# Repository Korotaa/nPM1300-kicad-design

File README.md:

# nPM1300-kicad-design

- Power Management IC
- USB type c receptacle
- Very low capacitance ESD protection : SOT23-6L
- 4 layers PCB with 2 signals layer, 1 power plane (GND) and mixed layer

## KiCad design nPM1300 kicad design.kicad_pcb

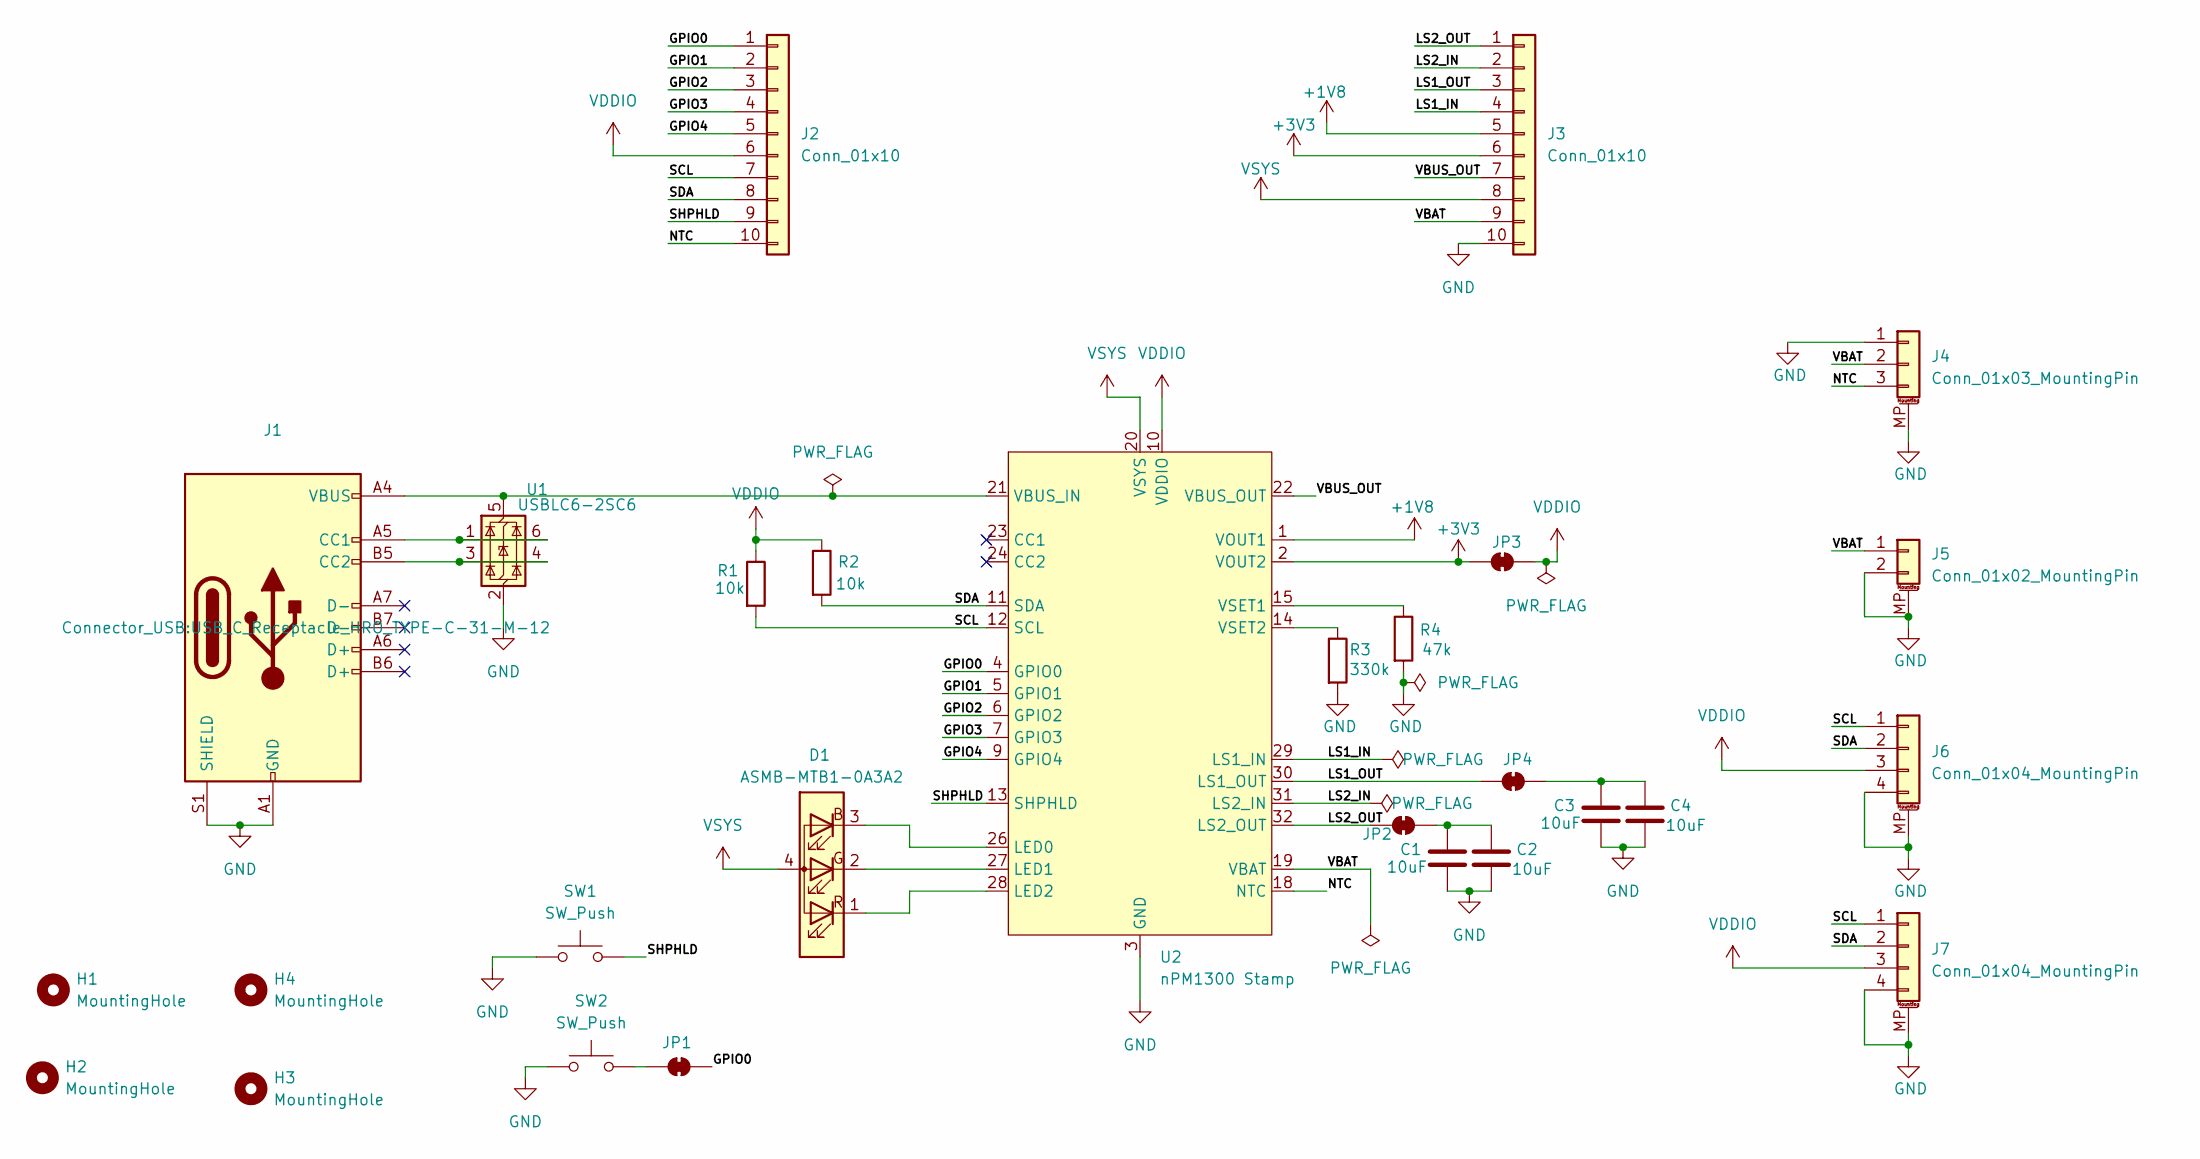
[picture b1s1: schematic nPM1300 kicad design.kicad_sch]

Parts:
C1, C2, C3, C4: 10uF; C_0603_1608Metric_Pad1.08x0.95mm_HandSolder
D1: ASMB-MTB1-0A3A2; LED_Avago_PLCC4_3.2x2.8mm_CW
H1, H2, H3, H4: MountingHole; MountingHole_2.2mm_M2_DIN965_Pad
J1: USB_C_Receptacle_USB2.0_14P; USB_C_Receptacle_HRO_TYPE-C-31-M-12
J2, J3: Conn_01x10; PinHeader_1x10_P1.00mm_Vertical
J4: Conn_01x03_MountingPin; JST_SH_SM03B-SRSS-TB_1x03-1MP_P1.00mm_Horizontal
J5: Conn_01x02_MountingPin; JST_SH_SM02B-SRSS-TB_1x02-1MP_P1.00mm_Horizontal
J6, J7: Conn_01x04_MountingPin; JST_SH_SM04B-SRSS-TB_1x04-1MP_P1.00mm_Horizontal
JP1, JP2, JP3, JP4: SolderJumper_2_Bridged; SolderJumper-2_P1.3mm_Bridged_Pad1.0x1.5mm
R1, R2: 10k; R_0402_1005Metric_Pad0.72x0.64mm_HandSolder
R3: 330k; R_0402_1005Metric_Pad0.72x0.64mm_HandSolder
R4: 47k; R_0402_1005Metric_Pad0.72x0.64mm_HandSolder
SW1, SW2: SW_Push; SW_Push_1P1T_NO_Vertical_Wuerth_434133025816
U1: USBLC6-2SC6; SOT-23-6
U2: nPM1300 Stamp; nPM1300-Stamp_18x18_Pitch2mm

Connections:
+1V8: J3.5, U2.1 (VOUT1)
+3V3: J3.6, JP3.1 (A), U2.2 (VOUT2)
/GPIO0: J2.1, JP1.2 (B), U2.4 (GPIO0)
/GPIO1: J2.2, U2.5 (GPIO1)
/GPIO2: J2.3, U2.6 (GPIO2)
/GPIO3: J2.4, U2.7 (GPIO3)
/GPIO4: J2.5, U2.9 (GPIO4)
/LS1_IN: J3.4, U2.29 (LS1_IN)
/LS1_OUT: J3.3, JP4.1 (A), U2.30 (LS1_OUT)
/LS2_IN: J3.2, U2.31 (LS2_IN)
/LS2_OUT: J3.1, JP2.1 (A), U2.32 (LS2_OUT)
/NTC: J2.10, J4.3, U2.18 (NTC)
/SCL: J2.7, J6.1, J7.1, R1.2, U2.12 (SCL)
/SDA: J2.8, J6.2, J7.2, R2.2, U2.11 (SDA)
/SHPHLD: J2.9, SW1.2, U2.13 (SHPHLD)
/VBAT: J3.9, J4.2, J5.1, U2.19 (VBAT)
/VBUS_OUT: J3.7, U2.22 (VBUS_OUT)
GND: C1.2, C2.2, C3.2, C4.2, J1.A1 (GND), J1.A12 (GND), J1.B1 (GND), J1.B12 (GND), J1.S1 (SHIELD), J3.10, J4.1, J4.MP (MountPin), J5.2, J5.MP (MountPin), J6.4, J6.MP (MountPin), J7.4, J7.MP (MountPin), R3.2, R4.2, SW1.1, SW2.1, U1.2 (GND), U2.3 (GND), U2.8 (GND), U2.16 (GND), U2.17 (GND), U2.25 (GND)
unnamed: D1.3 (BK), U2.26 (LED0)
unnamed: D1.2 (GK), U2.27 (LED1)
unnamed: D1.1 (RK), U2.28 (LED2)
unnamed: J1.A5 (CC1), U1.1 (I/O1), U1.6 (I/O1)
unnamed: J1.B5 (CC2), U1.3 (I/O2), U1.4 (I/O2)
unnamed: JP1.1 (A), SW2.2
unnamed: C1.1, C2.1, JP2.2 (B)
unnamed: C3.1, C4.1, JP4.2 (B)
unnamed: J1.A4 (VBUS), J1.A9 (VBUS), J1.B4 (VBUS), J1.B9 (VBUS), U1.5 (VBUS), U2.21 (VBUS_IN)
unnamed: R4.1, U2.15 (VSET1)
unnamed: R3.1, U2.14 (VSET2)
VDDIO: J2.6, J6.3, J7.3, JP3.2 (B), R1.1, R2.1, U2.10 (VDDIO)
VSYS: D1.4 (A), J3.8, U2.20 (VSYS)

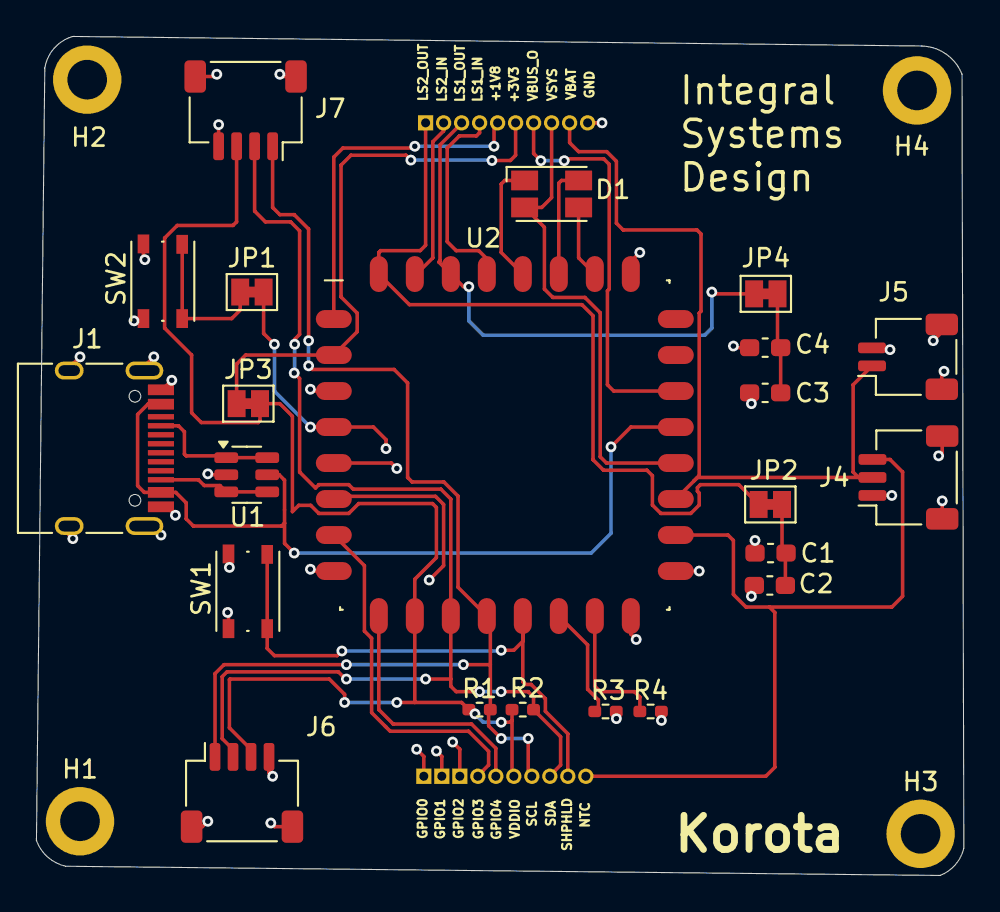
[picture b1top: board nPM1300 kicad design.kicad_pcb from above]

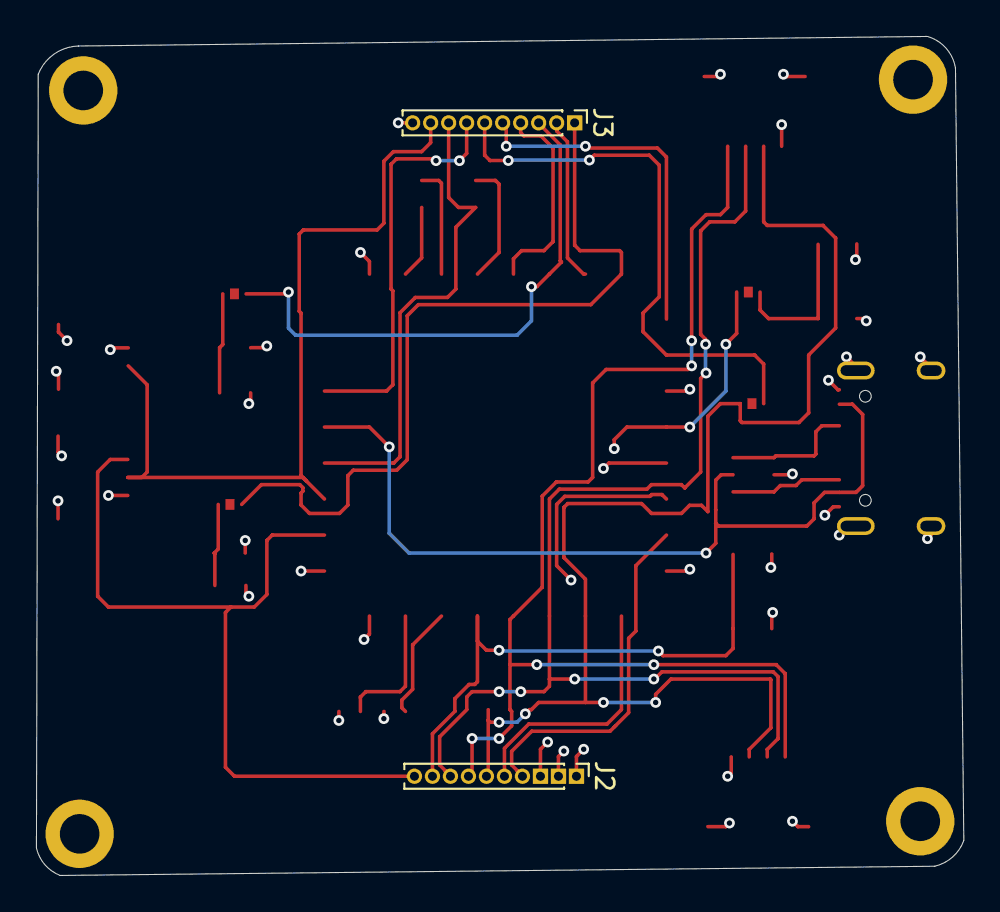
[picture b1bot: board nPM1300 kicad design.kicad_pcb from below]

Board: 4 copper layers, 51.5 x 46.6 mm, 28 parts (2 on the bottom side), 31 nets.

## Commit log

2024-10-14 PCB design
